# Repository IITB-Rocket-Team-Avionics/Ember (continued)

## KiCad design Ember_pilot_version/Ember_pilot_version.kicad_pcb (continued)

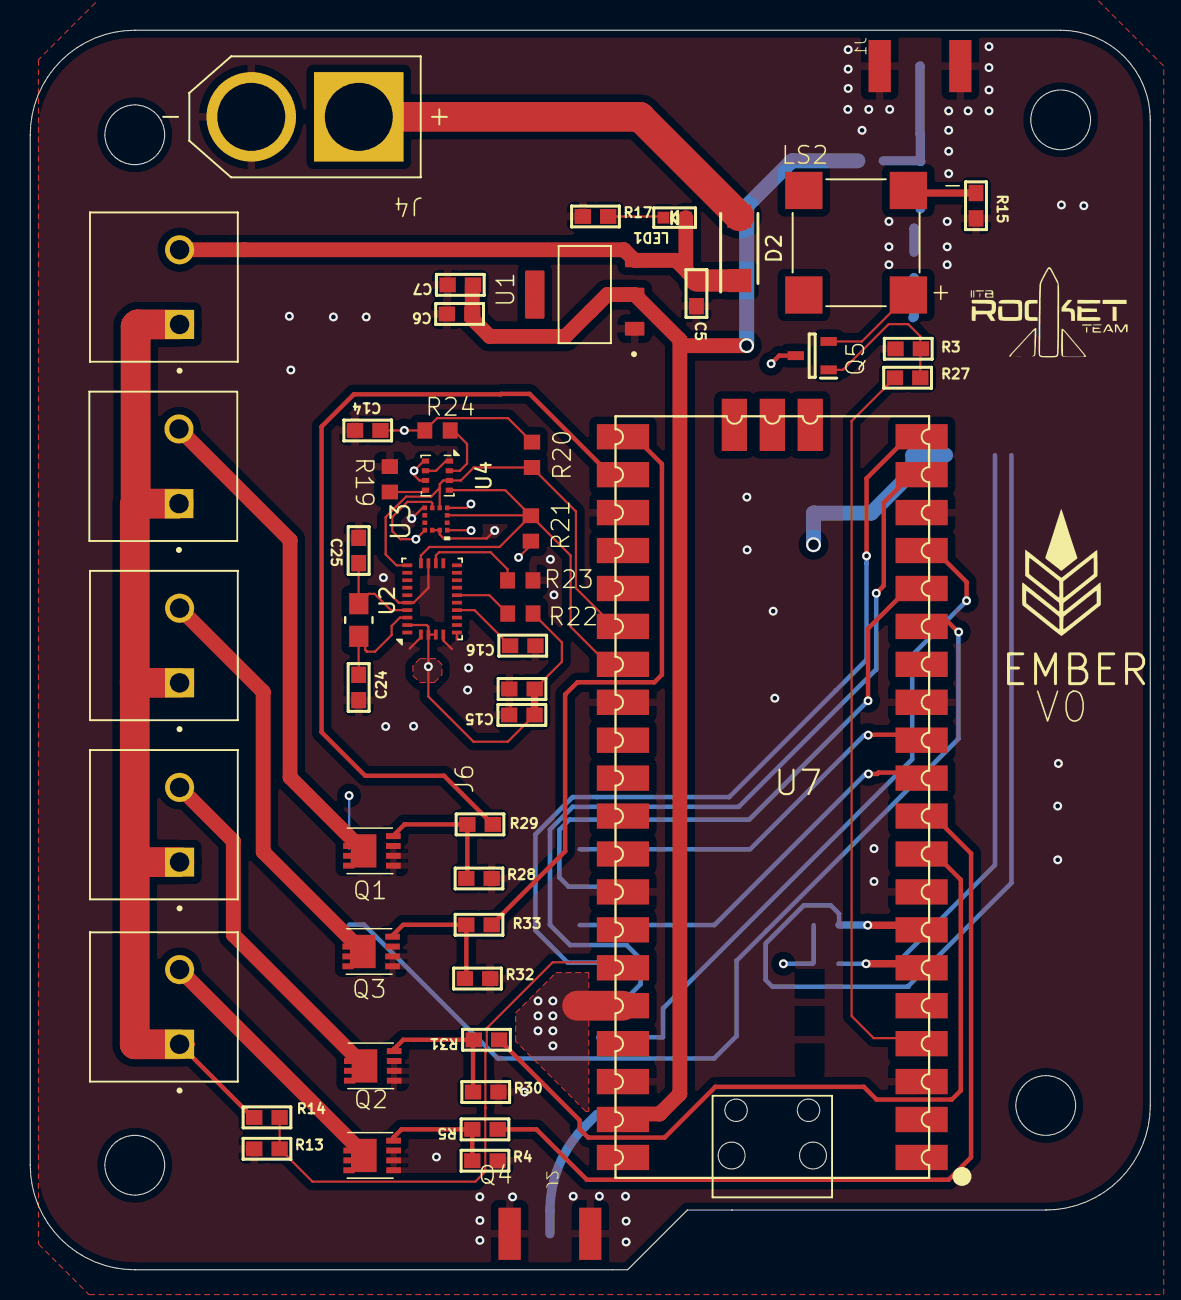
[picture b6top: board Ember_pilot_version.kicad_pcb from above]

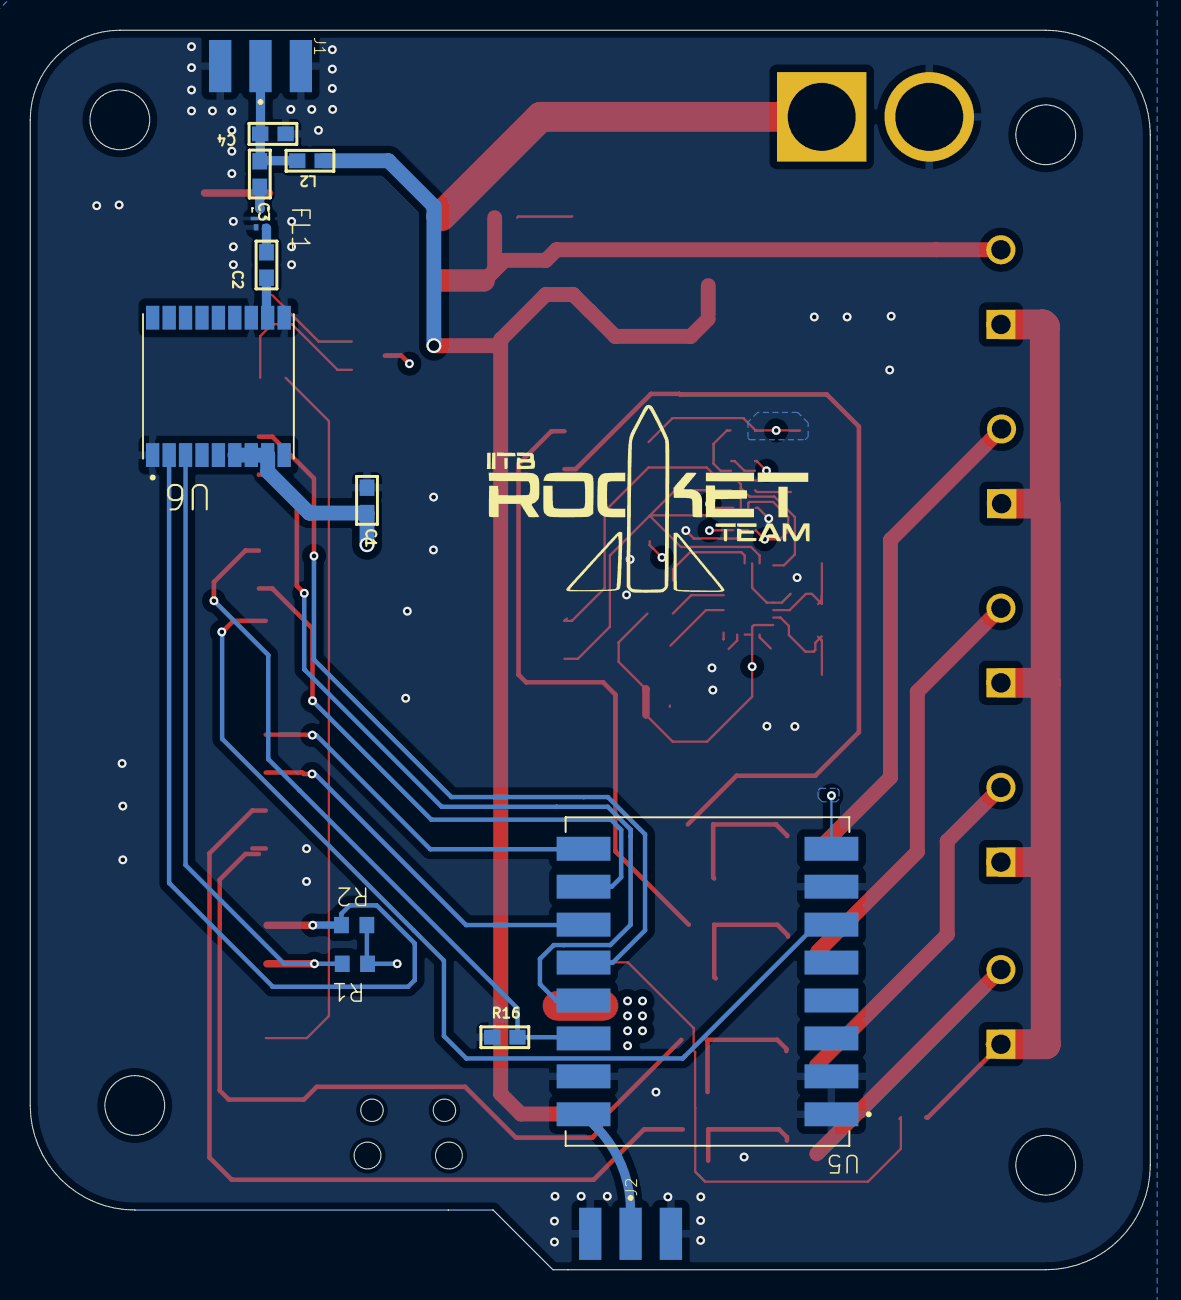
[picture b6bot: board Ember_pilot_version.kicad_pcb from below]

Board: 4 copper layers, 75.0 x 83.0 mm, 62 parts (13 on the bottom side), 47 nets.

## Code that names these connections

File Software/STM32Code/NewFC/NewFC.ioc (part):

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Mcu.Name=STM32F411C(C-E)Ux
Mcu.Package=UFQFPN48
Mcu.UserName=STM32F411CEUx
PA10.Mode=Asynchronous
PA10.Signal=USART1_RX
PA13.Mode=Serial_Wire
PA13.Signal=SYS_JTMS-SWDIO
PA14.Mode=Serial_Wire
PA14.Signal=SYS_JTCK-SWCLK
PA5.Mode=Full_Duplex_Master
PA5.Signal=SPI1_SCK
PA6.Mode=Full_Duplex_Master
PA6.Signal=SPI1_MISO
PA7.Mode=Full_Duplex_Master
PA7.Signal=SPI1_MOSI
PA9.Mode=Asynchronous
PA9.Signal=USART1_TX
PB6.Mode=I2C
PB6.Signal=I2C1_SCL
PB7.Mode=I2C
PB7.Signal=I2C1_SDA
PC14-OSC32_IN.Mode=LSE-External-Oscillator
PC14-OSC32_IN.Signal=RCC_OSC32_IN
PC15-OSC32_OUT.Mode=LSE-External-Oscillator
PC15-OSC32_OUT.Signal=RCC_OSC32_OUT
PH0\ -\ OSC_IN.Mode=HSE-External-Oscillator
PH0\ -\ OSC_IN.Signal=RCC_OSC_IN
PH1\ -\ OSC_OUT.Mode=HSE-External-Oscillator
PH1\ -\ OSC_OUT.Signal=RCC_OSC_OUT
RCC.HSE_VALUE=25000000
RCC.SYSCLKFreq_VALUE=25000000
RCC.SYSCLKSource=RCC_SYSCLKSOURCE_HSE
board=custom

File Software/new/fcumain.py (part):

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        # beep_task drains it without blocking the loop.
        self._beep_queue = []

        self.drogue_pin  = None
        self.drogue2_pin = None
        self.main_pin    = None
        self.main2_pin   = None

        self.buzzer = None
        self.led    = None
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        self.led    = Pin(25, Pin.OUT)
        self.led0   = Pin(0,  Pin.OUT);  self.led0.value(0)
        self.led1   = Pin(1,  Pin.OUT);  self.led1.value(0)
        self.buzzer = PWM(Pin(2));       self.buzzer.duty_u16(0)

        self.drogue_pin  = Pin(6,  Pin.OUT);  self.drogue_pin.value(0)
        self.drogue2_pin = Pin(7,  Pin.OUT);  self.drogue2_pin.value(0)
        self.main_pin    = Pin(16, Pin.OUT);  self.main_pin.value(0)
        self.main2_pin   = Pin(17, Pin.OUT);  self.main2_pin.value(0)

        # ── Primary pyro continuity ADC ───────────────────────────────────────
        self.adc_pyro_drogue = ADC(Pin(26))   # GP26 = PYRO_DROGUE
        self.adc_pyro_main   = ADC(Pin(27))   # GP27 = PYRO_MAIN
        print('[FCU] Pyro ADC ready (GP26=DROGUE, GP27=MAIN)')

        # ── UART to TDU ───────────────────────────────────────────────────────
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                        self._flicker_event = True
                        self.failure('DROGUE at ' + str(self.t_events[2]))
                        for _ in range(3):
                            self.drogue_pin.value(1)
                            self.drogue2_pin.value(1)
                            sleep_ms(300)
                            self.drogue_pin.value(0)
                            self.drogue2_pin.value(0)
                            sleep_ms(100)

                # ── DROGUE ────────────────────────────────────────────────────
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                        self.t_events[3] = self.t_log
                        self._flicker_event = True
                        for _ in range(3):
                            self.main_pin.value(1)
                            self.main2_pin.value(1)
                            sleep_ms(300)
                            self.main_pin.value(0)
                            self.main2_pin.value(0)
                            sleep_ms(100)

                # ── MAIN ──────────────────────────────────────────────────────
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                        self.failure('LANDED at ' + str(self.t_events[4]))

                # Always de-assert pyros
                self.drogue_pin.value(0);  self.drogue2_pin.value(0)
                self.main_pin.value(0);    self.main2_pin.value(0)
                self.last_t_log = self.t_log

            except Exception as e:
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
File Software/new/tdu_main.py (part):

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        self.fcu_connected = False

        # Camera / secondary drogue
        self.cam_pin     = None
        self.g_drogue_pin= None

        self.lora_frame  = bytearray(LORA_LEN)
        self.gps_echo    = bytearray(ustruct.calcsize(GPS_ECHO_FMT))
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
        # ── GPIO ──────────────────────────────────────────────────────────────
        self.led    = Pin(25, Pin.OUT)
        self.buzzer = PWM(Pin(18))
        self.buzzer.duty_u16(0)

        self.cam_pin      = Pin(15, Pin.OUT); self.cam_pin.value(0)
        self.g_drogue_pin = Pin(20, Pin.OUT); self.g_drogue_pin.value(0)

        # ── B2B UART to FCU ───────────────────────────────────────────────────
        self.b2b = UART(0, baudrate=115200, tx=Pin(0), rx=Pin(1))
        print('[TDU] B2B UART ready (waiting for FCU_INIT_OK)')

        # ── GPS ───────────────────────────────────────────────────────────────
        gps_reset = Pin(17, Pin.OUT)
        gps_reset.value(0)
        sleep_ms(100)
        gps_reset.value(1)
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
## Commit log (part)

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2025-10-11 Added KiCad project file
2025-10-11 Edited readme
2025-10-11 edited readme
    Add project description for Ember flight computer.
2025-10-12 Edited the logo
2025-10-17 Added the libraries
2025-10-19 Added power supply
2025-10-19 Added the flash, XTAL remaining
2025-10-19 Added xtal
2025-10-21 Sensors done, some issues to be resolved
2025-10-23 crystal error resolved
2025-10-23 Added pilot board
2025-10-24 gnss added
2025-10-25 LoRa, Buck converter and pyro (partially) added
2025-10-29 file issues resolved
2025-10-30 Added Final Iterations in pilot version
2025-10-31 changed buzzer circuit, pyro mosfets and finalized connections
2025-10-31 completed
2025-10-31 issues resolved
2025-11-02 routing started
2025-11-03 initial layout done, rf traces remaining
2025-11-04 RF traces done with some design changes
2025-11-04 A few slight changes
2025-11-04 Optimized routings
2025-11-08 board finalised
2025-11-09 corrected some missed issues
2025-12-08 power supply changes to LDO
2025-12-08 Updated hirarchy and structure
2025-12-25 Base requirements added in schemcatics
2026-02-02 Added everything till test launch 1 prep
2026-02-12 Added Ember_v0.2
2026-02-14 Roughly added the strain gauge thingy
2026-02-14 Added the files for RF board
2026-03-09 anything until test launch prep
2026-03-19 all until 19 mar
2026-03-21 Ember V0.2 routing halfway done
2026-03-21 Ahaan's RF Headers 16 to 4
2026-03-22 RF Board PCB Attempt 1
2026-03-22 main board routing started
2026-03-23 Some corrections done and main board routing halfway done
2026-03-25 Some changes on V0.2 layout
2026-03-27 board route almost complete
2026-03-27 did some graphic things on silkscreen
2026-03-28 Added some assets and V0.2 is sent for review
2026-03-28 All relevant DRC errors are resolved
2026-03-28 All routings completed, Lisan Al-gaib!
2026-03-30 TDU board LDO is replaced by AP63205
2026-03-30 All changes and things are done in both FCU and TDU - Lisan Al-gaib!
2026-04-01 v0.2 and RF v0 sent for fab - Lisan Al-gaib
2026-05-09 Experimental files on TDU FCU arrangement
2026-05-09 gitignore
2026-06-26 Added the irec 2026 fcu data
2026-06-29 new fcu main
